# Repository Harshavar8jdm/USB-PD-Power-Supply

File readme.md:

# CH224A USB Power Delivery (PD) Trigger Board

A 4-layer custom printed circuit board designed around the WCH CH224A USB Power Delivery sink controller. This board requests discrete voltage profiles from 5V up to 28V (USB PD 3.0 / 3.1 EPR) at power levels up to 100W, making standard USB-C PD power supplies usable for bench instruments, prototypes, and DC-powered devices.

---

## Board Visuals

### 3D Renders
| Top View | Bottom View |
| :---: | :---: |
|  |  |

---

## Features

* **Wide Voltage Range:** Requests 5V, 9V, 12V, 20V, or 28V output based on switch configuration or digital override.
* **Dual Control Modes:** Manual hardware selection via a 3-position DIP switch, or digital register control over an onboard I2C header.
* **Visual Status Indicators:** Dedicated surface-mount LEDs for each voltage profile (5V, 9V, 12V, 20V, 28V).
* **High-Current Power Path:** Solid copper pours on VBUS and GND pads of the 16-pin USB-C receptacle to reduce resistance and thermal rise under 5A loads.
* **4-Layer PCB Layout:** Dedicated internal ground planes (Layer 2 & Layer 3) provide return paths and heat spreading.
* **Silkscreen Truth Table:** Printed reference table on top silk for direct voltage-setting configuration without consulting external documentation.
* **Output Termination:** 2-pin Phoenix screw terminal block for connection to external loads.

---

## Specifications

| Parameter | Specification |
| :--- | :--- |
| **Input Connector** | 16-Pin USB Type-C Receptacle (`J2`) |
| **Output Connector** | 2-Pin Screw Terminal Block (`J1`) |
| **Controller IC** | WCH CH224A |
| **Supported Voltages** | 5V, 9V, 12V, 20V, 28V (EPR) |
| **Maximum Current** | Up to 5A |
| **Maximum Power** | 100W |
| **Control Interface** | 3-position DIP Switch (`S1`, `S2`, `S3`) & 3-pin I2C Header (`J3`) |
| **Stackup** | 4-layer (Signal / GND / GND / Signal) |

---

## Voltage Selection (DIP Switch Truth Table)

The DIP switch (`S1`, `S2`, `S3`) controls the configuration pins of the CH224A. Use the following logic combinations to select the target output voltage:

| S1 | S2 | S3 | Selected Output Voltage (VOUT) |
| :---: | :---: | :---: | :---: |
| `0` | `0` | `0` | **5V** |
| `1` | `1` | `1` | **9V** |
| `1` | `1` | `0` | **12V** |
| `1` | `0` | `0` | **20V** |
| `1` | `0` | `1` | **28V** |

> **Note:** The truth table is also silkscreened on the top layer of the PCB for quick reference.

---

## PCB Layout & Schematic

### Schematic Diagram
* [View Schematic (PDF)](Images/schematic.pdf)

### Layer Stackup & Routing
| Layer | Layout Image | Description |
| :--- | :---: | :--- |
| **Top Layer (F.Cu)** |  | Signal routing, component placement, voltage LEDs, and `V_USB` power pours. |
| **Inner Layer 1 (In1.Cu)** |  | Continuous Ground Plane (GND). |
| **Inner Layer 2 (In2.Cu)** |  | Continuous Ground Plane (GND). |
| **Bottom Layer (B.Cu)** |  | Low-speed signal routing and DIP switch interconnects. |

---

## Hardware Architecture

### High-Current Design Considerations
* **Solid Copper Pours:** VBUS and GND pads on the USB-C receptacle avoid thermal relief necking to maximize current delivery up to 5A without excessive trace heating.
* **Thermal Management:** Dual internal ground planes serve as an integrated thermal heat spreader for the CH224A IC and power paths.

### Microcontroller Interface (I2C Header - J3)
The `J3` header exposes the I2C bus pins (`SCL`, `GND`, `SDA`) connected to the CH224A controller, allowing an external host MCU (e.g., STM32, ESP32, AVR) to read status registers or programmatically switch profiles.

* **Pinout:**
  1. `SCL` (I2C Clock)
  2. `GND` (Ground)
  3. `SDA` (I2C Data)
* **Bus Pull-ups:** The board omits dedicated pull-up resistors on SDA/SCL to minimize component count. Activate the internal pull-up resistors on the host microcontroller's GPIO pins when using this interface.

---

## Repository File Structure

```text
├── Images/
│   ├── 3d_render_top.png
│   ├── 3d_render_bottom.png
│   ├── pcb_layout_fcu.png
│   ├── pcb_layout_in1.png
│   ├── pcb_layout_in2.png
│   ├── pcb_layout_bcu.png
│   └── schematic.pdf
└── README.md

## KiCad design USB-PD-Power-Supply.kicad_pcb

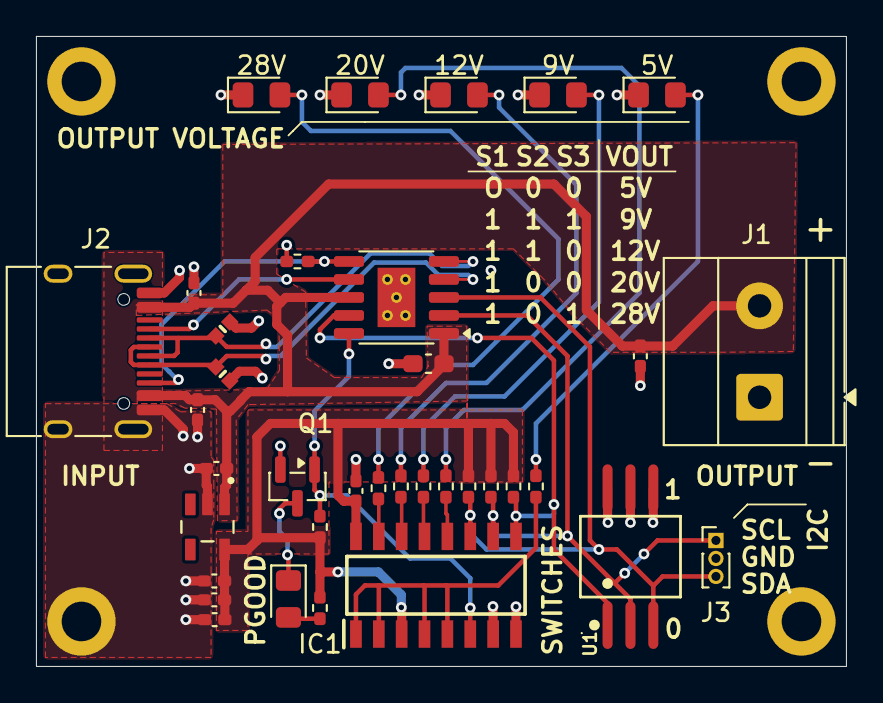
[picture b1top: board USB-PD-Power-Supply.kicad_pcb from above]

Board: 4 copper layers, 45.0 x 35.0 mm, 40 parts (0 on the bottom side), 23 nets.

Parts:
5V, 9V, 12V, 20V, 28V: LED; LED_0805_2012Metric_Pad1.15x1.40mm_HandSolder
C1, C2, C4, C5, C6, C7, C8, C9: 100nF; C_0402_1005Metric_Pad0.74x0.62mm_HandSolder
C3: 1uF/50V; C_0603_1608Metric_Pad1.08x0.95mm_HandSolder
D1: LED; LED_0805_2012Metric_Pad1.15x1.40mm_HandSolder
D2, D3: TVS; DIONC1006X55N
H1, H2, H3, H4: MountingHole_Pad; MountingHole_2.2mm_M2_DIN965_Pad
IC1: MC14051BDR2G; SOIC127P600X175-16N
J1: Screw_Terminal_01x02; TerminalBlock_Phoenix_MKDS-1,5-2-5.08_1x02_P5.08mm_Horizont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
J2: USB_C_Receptacle_USB2.0_16P; USB_C_Receptacle_HRO_TYPE-C-31-M-12
J3: Conn_01x03_Pin; PinHeader_1x03_P1.00mm_Vertical
Q1: 2N7002; SOT-23
R1, R6, R7, R8, R9, R10, R11: 1K; R_0402_1005Metric_Pad0.72x0.64mm_HandSolder
R2, R3, R4, R5: 10K; R_0402_1005Metric_Pad0.72x0.64mm_HandSolder
U1: SW-SMD_DSHP03TS-S; SW-SMD_DSHP03TS-S_DSHP03TS-S_C319051
U2: CH224A; SSOP-10-1EP_3.9x4.9mm_P1mm_EP2.1x3.3mm
U3: TPS70933DBVR; SOT95P280X145-5N

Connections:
+3.3V: C5.1, C7.1, C8.1, C9.1, IC1.3 (X), IC1.16 (VDD), R1.1, R2.1, R3.1, R4.1, R5.1, U3.5 (OUT)
/CC1: J2.A5 (CC1), U2.7 (CC1)
/CC2: J2.B5 (CC2), R6.1, U2.6 (CC2)
/CFB1: IC1.9 (C), R3.2, U1.1, U2.9 (CFG1)
/CFB2_SCL: IC1.10 (B), J3.1, R4.2, U1.2, U2.2 (CFG2)
/CFB3_SDA: IC1.11 (A), J3.3, R5.2, U1.3, U2.3 (CFG3)
/PG: IC1.6 (INH), Q1.1 (G), R2.2, U2.10 (PG)
/USB_N: D2.1, J2.A7 (D-), J2.B7 (D-), U2.5 (DM)
/USB_P: D3.1, J2.A6 (D+), J2.B6 (D+), U2.4 (DP)
GND: 5V.1 (K), 9V.1 (K), 12V.1 (K), 20V.1 (K), 28V.1 (K), C1.2, C2.2, C3.1, C4.2, C5.2, C6.2, C7.2, C8.2, C9.2, D2.2, D3.2, H1.1 (1_1), H2.1 (1_1), H3.1 (1_1), H4.1 (1_1), IC1.7 (VEE), IC1.8 (VSS), J1.1, J2.A1 (GND), J2.A12 (GND), J2.B1 (GND), J2.B12 (GND), J2.SH (SHIELD), J3.2, Q1.2 (S), R6.2, U1.4, U1.5, U1.6, U2.11 (GND), U2.12, U3.2 (GND)
unnamed: D1.2 (A), R1.2
unnamed: D1.1 (K), Q1.3 (D)
unnamed: 28V.2 (A), R7.1
unnamed: 20V.2 (A), R8.1
unnamed: 12V.2 (A), R9.1
unnamed: 9V.2 (A), R10.1
unnamed: 5V.2 (A), R11.1
unnamed: IC1.13 (X0), R10.2
unnamed: IC1.14 (X1), R9.2
unnamed: IC1.15 (X2), R7.2
unnamed: IC1.12 (X3), R8.2
unnamed: IC1.1 (X4), IC1.2 (X6), IC1.4 (X7), IC1.5 (X5), R11.2
V_USB: C1.1, C2.1, C3.2, C4.1, C6.1, J1.2, J2.A4 (VBUS), J2.A9 (VBUS), J2.B4 (VBUS), J2.B9 (VBUS), U2.1 (VHV), U2.8 (VBUS), U3.1 (IN)
